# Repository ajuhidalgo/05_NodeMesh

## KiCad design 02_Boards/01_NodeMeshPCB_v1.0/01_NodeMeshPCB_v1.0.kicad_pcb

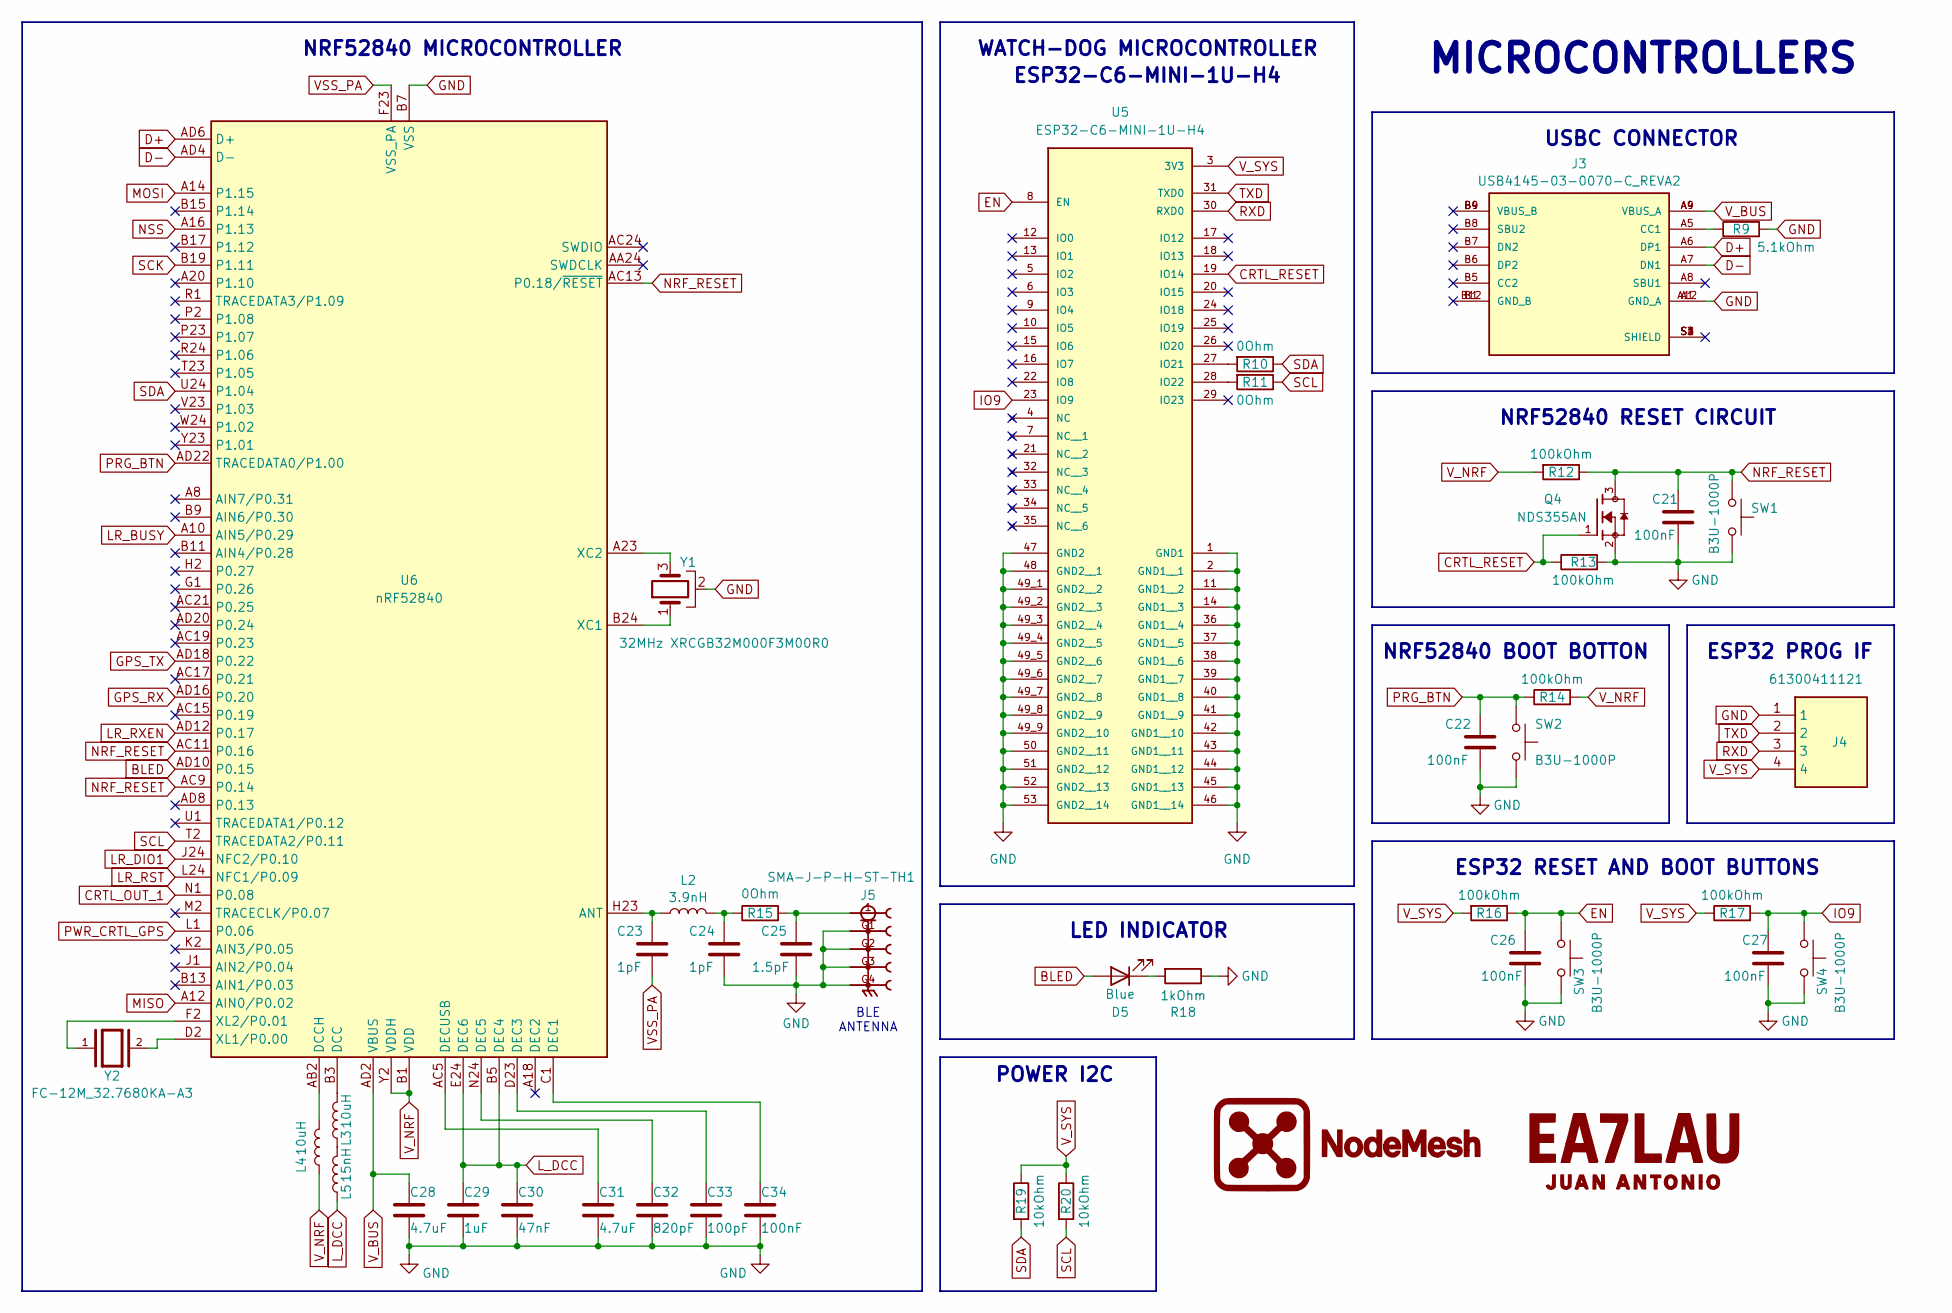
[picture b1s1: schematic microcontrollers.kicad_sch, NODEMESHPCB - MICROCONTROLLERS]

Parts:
C21, C22, C26, C27, C34: 100nF; C_0603_1608Metric
C23, C24: 1pF; C_0603_1608Metric
C25: 1.5pF; C_0603_1608Metric
C28, C31: 4.7uF; C_0603_1608Metric
C29: 1uF; C_0603_1608Metric
C30: 47nF; C_0603_1608Metric
C32: 820pF; C_0603_1608Metric
C33: 100pF; C_0603_1608Metric
D5: Blue; LED_0603_1608Metric
J3: USB4145-03-0070-C_REVA2; USB4145-03-0070-C; PARTREV A2
J4: 61300411121; Manufacturer_Part_Number 61300411121
J5: SMA-J-P-H-ST-TH1
L2: 3.9nH; L_0603_1608Metric
L3, L4: 10uH; L_0603_1608Metric
L5: 15nH; L_0603_1608Metric
Q4: NDS355AN; PARTREV 3
R9: 5.1kOhm; R_0603_1608Metric
R10, R11, R15: 0Ohm; R_0603_1608Metric
R12, R13, R14, R16, R17: 100kOhm; R_0603_1608Metric
R18: 1kOhm; R_0603_1608Metric
R19, R20: 10kOhm; R_0603_1608Metric
SW1, SW2, SW3, SW4: B3U-1000P; SW_SPST_B3U-1000P
U5: ESP32-C6-MINI-1U-H4; PARTREV 1.0
U6: nRF52840; Nordic_AQFN-73-1EP_7x7mm_P0.5mm
Y1: 32MHz XRCGB32M000F3M00R0; XRCGB32M000F3M00R0
Y2: FC-12M_32.7680KA-A3; FC-12M_327680KA-A3; PARTREV NA

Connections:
BLED: D5.2 (A), U6.AD10 (P0.15)
CRTL_OUT_1: U6.N1 (P0.08); also elsewhere on the board
CRTL_RESET: Q4.1, R13.1, U5.19 (IO14)
D+: J3.A6 (DP1), U6.AD6 (D+)
D-: J3.A7 (DN1), U6.AD4 (D-)
EN: C26.1, R16.1, SW3.1, U5.8 (EN)
GND: C21.2, C22.2, C24.2, C25.2, C26.2, C27.2, C28.2, C29.2, C30.2, C31.2, C32.2, C33.2, C34.2, J3.A1 (GND_A), J3.A12 (GND_A), J4.1, J5.G1, J5.G2, J5.G3, J5.G4, Q4.2, R9.2, R13.2, R18.1, SW1.2, SW2.2, SW3.2, SW4.2, U5.1 (GND1), U5.2 (GND1__1), U5.11 (GND1__2), U5.14 (GND1__3), U5.36 (GND1__4), U5.37 (GND1__5), U5.38 (GND1__6), U5.39 (GND1__7), U5.40 (GND1__8), U5.41 (GND1__9), U5.42 (GND1__10), U5.43 (GND1__11), U5.44 (GND1__12), U5.45 (GND1__13), U5.46 (GND1__14), U5.47 (GND2), U5.48 (GND2__1), U5.49_1 (GND2__2), U5.49_2 (GND2__3), U5.49_3 (GND2__4), U5.49_4 (GND2__5), U5.49_5 (GND2__6), U5.49_6 (GND2__7), U5.49_7 (GND2__8), U5.49_8 (GND2__9), U5.49_9 (GND2__10), U5.50 (GND2__11), U5.51 (GND2__12), U5.52 (GND2__13), U5.53 (GND2__14), U6.B7 (VSS), U6.EP (VSS), Y1.2; also elsewhere on the board
GPS_RX: U6.AD16 (P0.20); also elsewhere on the board
GPS_TX: U6.AD18 (P0.22); also elsewhere on the board
IO9: C27.1, R17.2, SW4.1, U5.23 (IO9)
LR_BUSY: U6.A10 (AIN5/P0.29); also elsewhere on the board
LR_DIO1: U6.J24 (NFC2/P0.10); also elsewhere on the board
LR_RST: U6.L24 (NFC1/P0.09); also elsewhere on the board
LR_RXEN: U6.AD12 (P0.17); also elsewhere on the board
L_DCC: C29.1, C30.1, L5.1, U6.B5 (DEC4), U6.E24 (DEC6)
MISO: U6.A12 (AIN0/P0.02); also elsewhere on the board
MOSI: U6.A14 (P1.15); also elsewhere on the board
NRF_RESET: C21.1, Q4.3, R12.1, SW1.1, U6.AC9 (P0.14), U6.AC11 (P0.16), U6.AC13 (P0.18/~RESET)
NSS: U6.A16 (P1.13); also elsewhere on the board
unnamed: C24.1, L2.2, R15.1
unnamed: C25.1, J5.1, R15.2
unnamed: D5.1 (K), R18.2
unnamed: J3.A5 (CC1), R9.1
unnamed: L3.1, L5.2
unnamed: R10.2, U5.27 (IO21)
unnamed: R11.2, U5.28 (IO22)
unnamed: C23.1, L2.1, U6.H23 (ANT)
unnamed: L3.2, U6.B3 (DCC)
unnamed: L4.2, U6.AB2 (DCCH)
unnamed: C34.1, U6.C1 (DEC1)
unnamed: C33.1, U6.D23 (DEC3)
unnamed: C32.1, U6.N24 (DEC5)
unnamed: C31.1, U6.AC5 (DECUSB)
unnamed: U6.B24 (XC1), Y1.1
unnamed: U6.A23 (XC2), Y1.3
unnamed: U6.D2 (XL1/P0.00), Y2.2
unnamed: U6.F2 (XL2/P0.01), Y2.1
PRG_BTN: C22.1, R14.1, SW2.1, U6.AD22 (TRACEDATA0/P1.00)
PWR_CRTL_GPS: U6.L1 (P0.06); also elsewhere on the board
RXD: J4.3, U5.30 (RXD0)
SCK: U6.B19 (P1.11); also elsewhere on the board
SCL: R11.1, R20.2, U6.T2 (TRACEDATA2/P0.11); also elsewhere on the board
SDA: R10.1, R19.2, U6.U24 (P1.04); also elsewhere on the board
TXD: J4.2, U5.31 (TXD0)
VSS_PA: C23.2, U6.F23 (VSS_PA)
V_BUS: C28.1, J3.A4 (VBUS_A), J3.A9 (VBUS_A), U6.AD2 (VBUS)
V_NRF: J4.4, L4.1, R12.2, R14.2, R16.2, R17.1, R19.1, R20.1, U5.3 (3V3), U6.A22 (VDD), U6.AD14 (VDD), U6.AD23 (VDD), U6.B1 (VDD), U6.W1 (VDD), U6.Y2 (VDDH); also elsewhere on the board

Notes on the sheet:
USBC CONNECTOR
ESP32-C6-MINI-1U-H4
NRF52840 MICROCONTROLLER
ESP32 RESET AND BOOT BUTTONS
WATCH-DOG MICROCONTROLLER
POWER I2C
LED INDICATOR
NRF52840 RESET CIRCUIT
ESP32 PROG IF
MICROCONTROLLERS
NRF52840 BOOT BOTTON
BLE ANTENNA

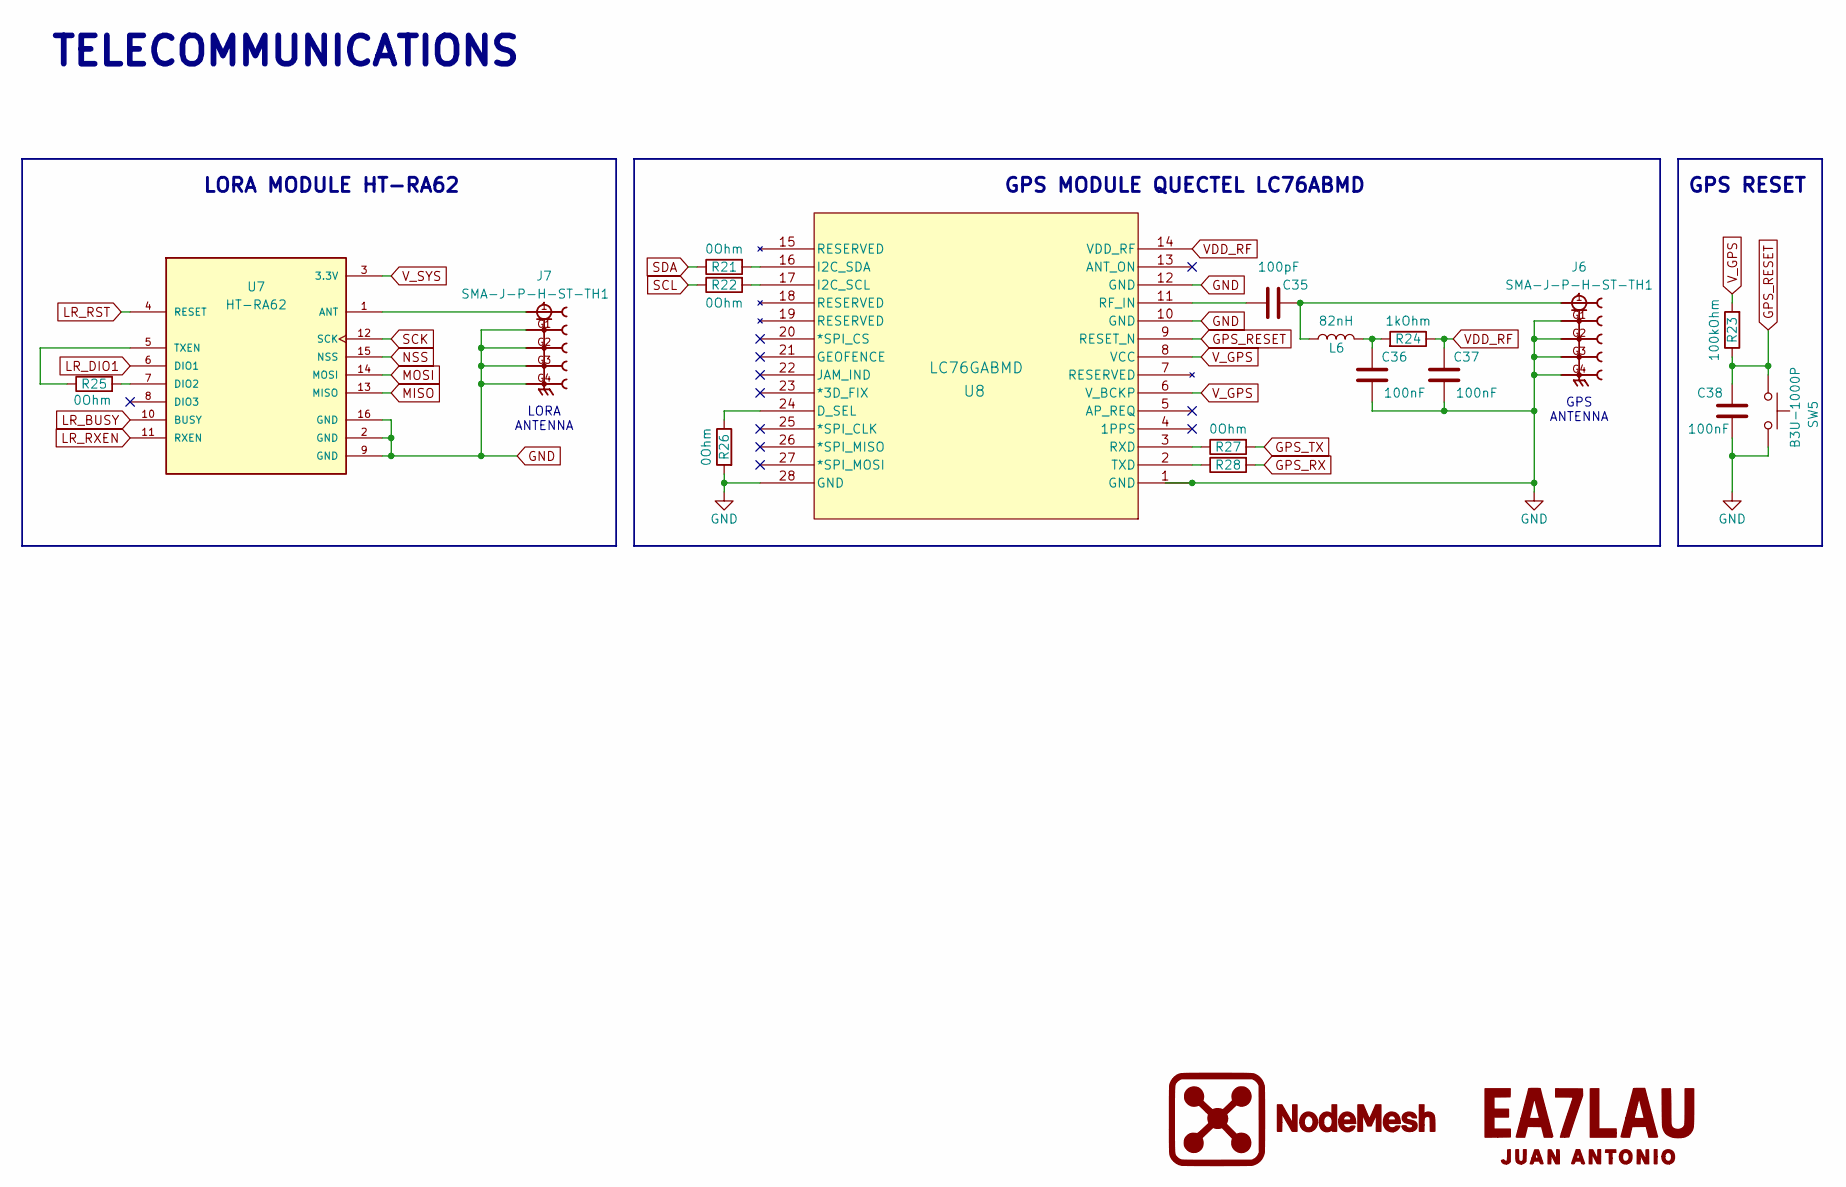
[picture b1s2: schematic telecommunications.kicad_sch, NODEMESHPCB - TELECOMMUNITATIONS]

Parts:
C35: 100pF; C_0603_1608Metric
C36, C37, C38: 100nF; C_0603_1608Metric
J6, J7: SMA-J-P-H-ST-TH1
L6: 82nH; L_0603_1608Metric
R21, R22, R25, R26, R27, R28: 0Ohm; R_0603_1608Metric
R23: 100kOhm; R_0603_1608Metric
R24: 1kOhm; R_0603_1608Metric
SW5: B3U-1000P; SW_SPST_B3U-1000P
U7: HT-RA62
U8: LC76GABMD

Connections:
GND: C36.2, C37.2, C38.2, J6.G1, J6.G2, J6.G3, J6.G4, J7.G1, J7.G2, J7.G3, J7.G4, R26.2, SW5.2, U7.2 (GND), U7.9 (GND), U7.16 (GND), U8.1 (GND), U8.10 (GND), U8.12 (GND), U8.28 (GND); also elsewhere on the board
GPS_RESET: C38.1, R23.1, SW5.1, U8.9 (RESET_N)
GPS_RX: R28.2; also elsewhere on the board
GPS_TX: R27.2; also elsewhere on the board
LR_BUSY: U7.10 (BUSY); also elsewhere on the board
LR_DIO1: U7.6 (DIO1); also elsewhere on the board
LR_RST: U7.4 (RESET); also elsewhere on the board
LR_RXEN: U7.11 (RXEN); also elsewhere on the board
MISO: U7.13 (MISO); also elsewhere on the board
MOSI: U7.14 (MOSI); also elsewhere on the board
NSS: U7.15 (NSS); also elsewhere on the board
unnamed: C35.2, J6.1, L6.2
unnamed: C36.1, L6.1, R24.2
unnamed: J7.1, U7.1 (ANT)
unnamed: R25.2, U7.7 (DIO2)
unnamed: R25.1, U7.5 (TXEN)
unnamed: R26.1, U8.24 (D_SEL)
unnamed: R22.2, U8.17 (I2C_SCL)
unnamed: R21.2, U8.16 (I2C_SDA)
unnamed: C35.1, U8.11 (RF_IN)
unnamed: R27.1, U8.3 (RXD)
unnamed: R28.1, U8.2 (TXD)
SCK: U7.12 (SCK); also elsewhere on the board
SCL: R22.1; also elsewhere on the board
SDA: R21.1; also elsewhere on the board
VDD_RF: C37.1, R24.1, U8.14 (VDD_RF)
V_GPS: R23.2, U8.6 (V_BCKP), U8.8 (VCC); also elsewhere on the board
V_NRF: U7.3 (3.3V); also elsewhere on the board

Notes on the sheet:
LORA ANTENNA
GPS MODULE QUECTEL LC76ABMD
LORA MODULE HT-RA62
GPS RESET
GPS ANTENNA
TELECOMMUNICATIONS

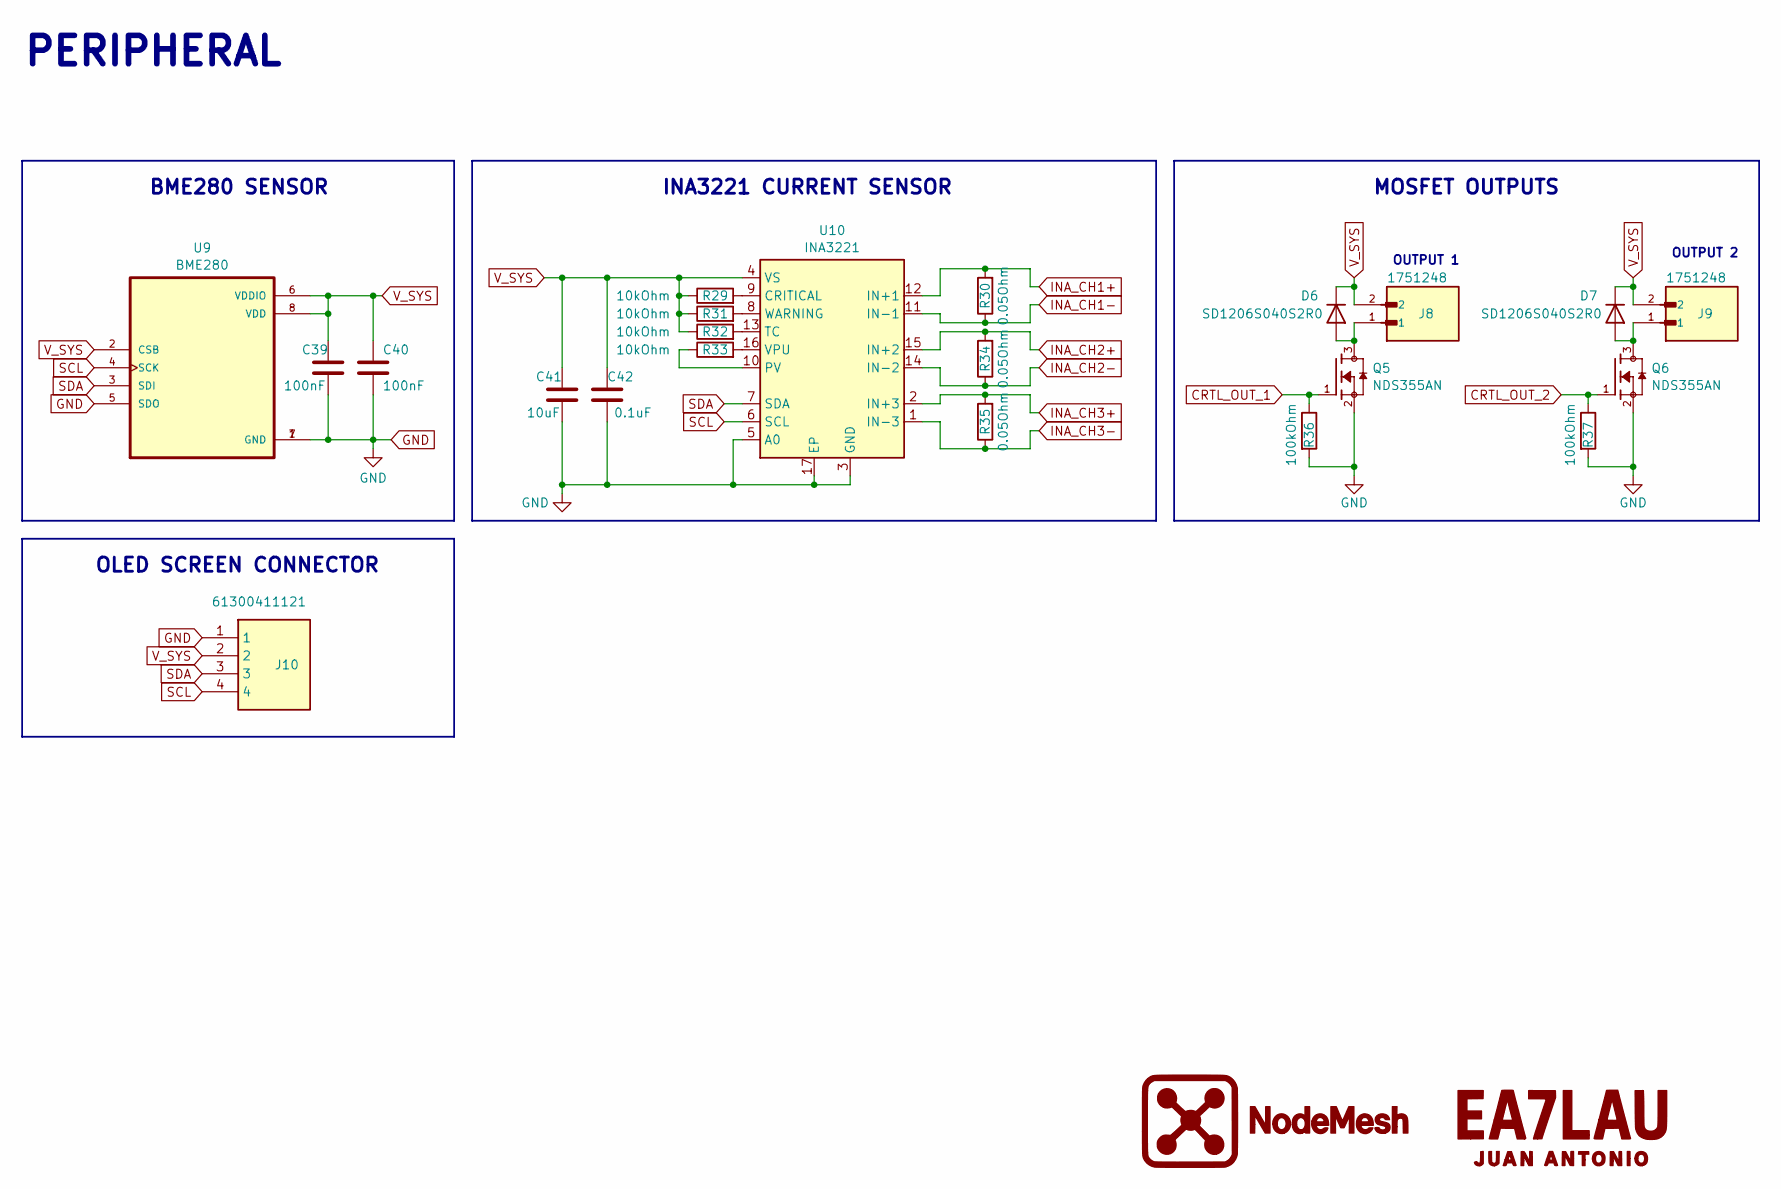
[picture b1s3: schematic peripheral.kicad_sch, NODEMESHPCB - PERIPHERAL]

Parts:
C39, C40: 100nF; C_0603_1608Metric
C41: 10uF; C_0603_1608Metric
C42: 0.1uF; C_0603_1608Metric
D6, D7: SD1206S040S2R0; D_1206_3216Metric
J8, J9: 1751248; TerminalBlock_Phoenix_MKDS-1,5-2-5.08_1x02_P5.08mm_Horizont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
J10: 61300411121; Manufacturer_Part_Number 61300411121
Q5, Q6: NDS355AN; PARTREV 3
R29, R31, R32, R33: 10kOhm; R_0603_1608Metric
R30, R34, R35: 0.05Ohm; R_1206_3216Metric
R36, R37: 100kOhm; R_0603_1608Metric
U9: BME280
U10: INA3221

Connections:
CRTL_OUT_1: Q5.1, R36.1; also elsewhere on the board
CRTL_OUT_2: Q6.1, R37.1
GND: C39.2, C40.2, C41.2, C42.2, J10.1, Q5.2, Q6.2, R36.2, R37.2, U9.1 (GND), U9.5 (SDO), U9.7 (GND), U10.3 (GND), U10.5 (A0), U10.17 (EP); also elsewhere on the board
INA_CH1+: R30.2, R34.1, U10.12 (IN+1), U10.14 (IN-2); also elsewhere on the board
INA_CH1-: R30.1, U10.11 (IN-1); also elsewhere on the board
INA_CH2+: R34.2, U10.15 (IN+2); also elsewhere on the board
INA_CH3+: R35.2, U10.2 (IN+3); also elsewhere on the board
INA_CH3-: R35.1, U10.1 (IN-3); also elsewhere on the board
unnamed: D6.2 (A), J8.1, Q5.3
unnamed: D7.2 (A), J9.1, Q6.3
unnamed: R29.2, U10.9 (CRITICAL)
unnamed: R33.1, U10.10 (PV)
unnamed: R32.2, U10.13 (TC)
unnamed: R33.2, U10.16 (VPU)
unnamed: R31.2, U10.8 (WARNING)
SCL: J10.4, U9.4 (SCK), U10.6 (SCL); also elsewhere on the board
SDA: J10.3, U9.3 (SDI), U10.7 (SDA); also elsewhere on the board
V_NRF: C39.1, C40.1, C41.1, C42.1, D6.1 (K), D7.1 (K), J8.2, J9.2, J10.2, R29.1, R31.1, R32.1, U9.2 (CSB), U9.6 (VDDIO), U9.8 (VDD), U10.4 (VS); also elsewhere on the board

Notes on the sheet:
BME280 SENSOR
OUTPUT 1
INA3221 CURRENT SENSOR
OUTPUT 2
MOSFET OUTPUTS
OLED SCREEN CONNECTOR
PERIPHERAL

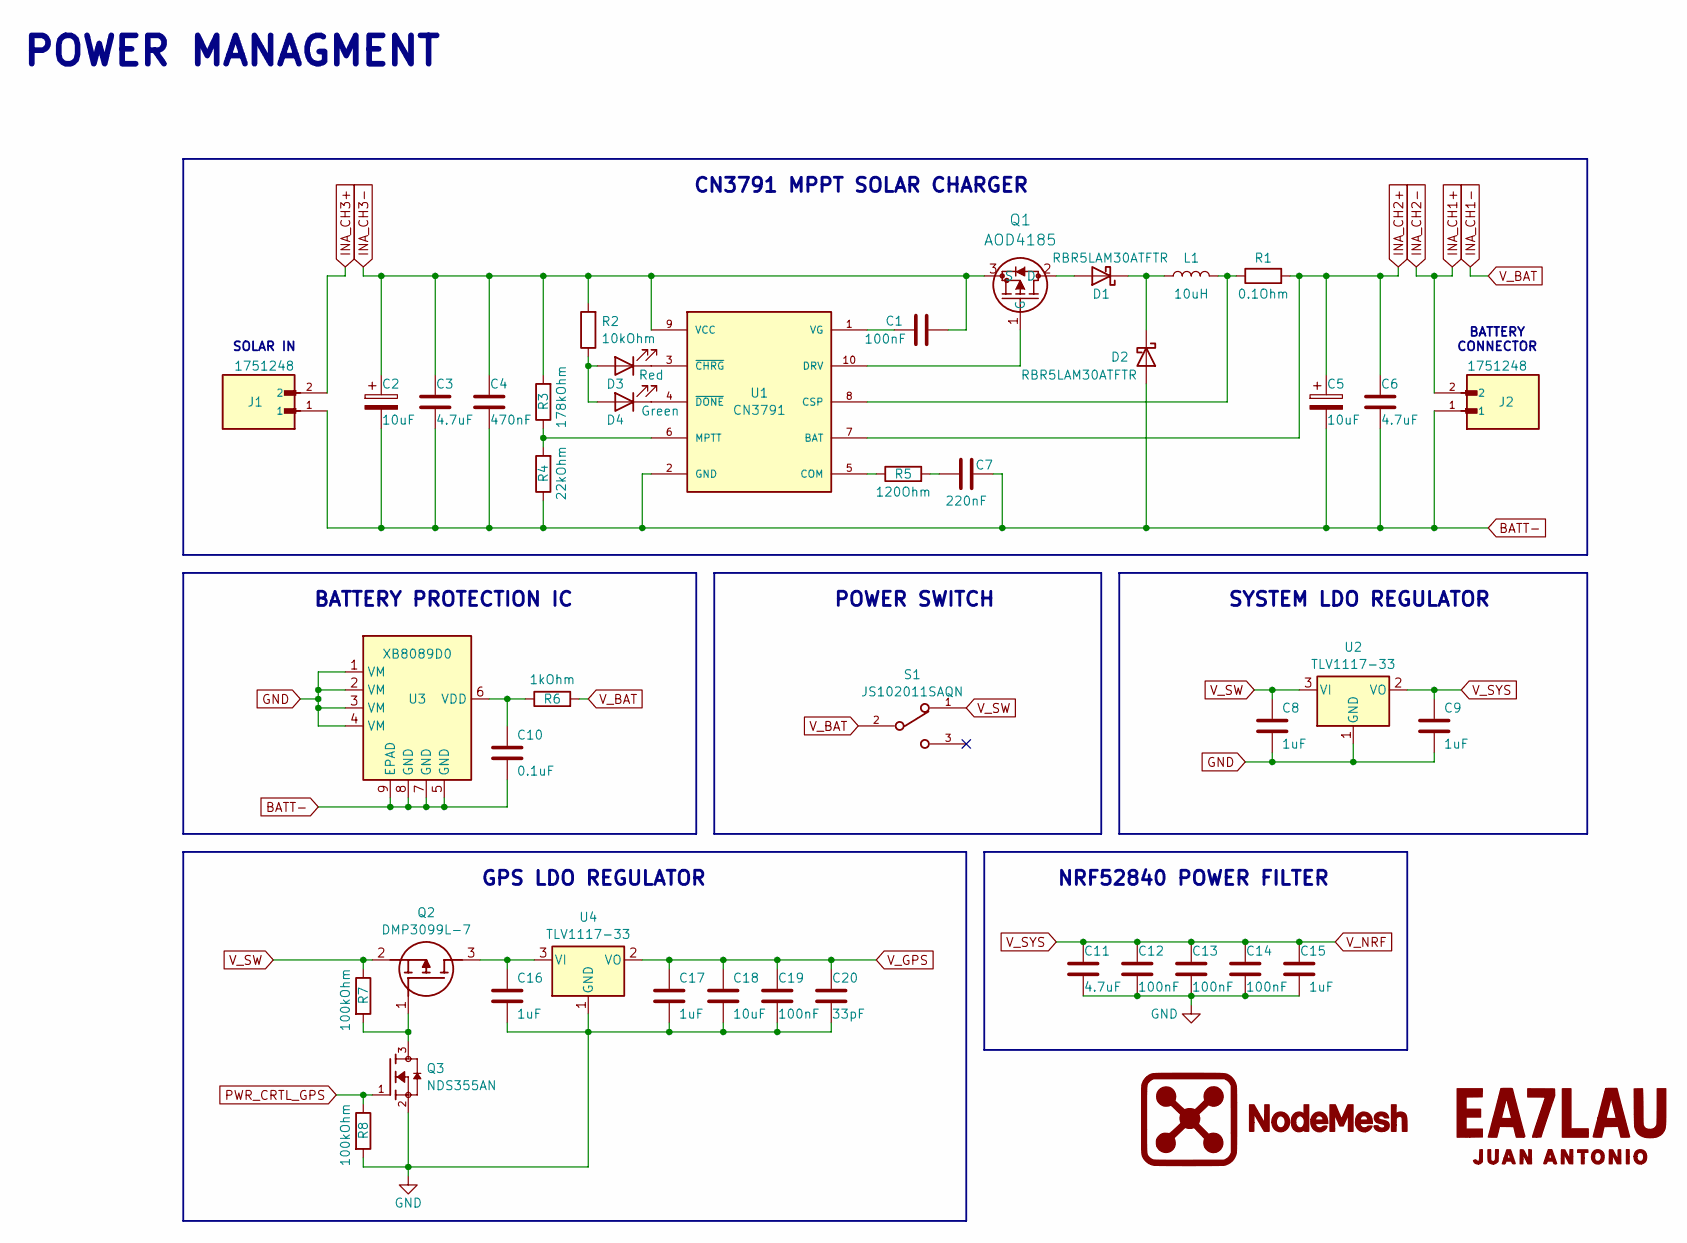
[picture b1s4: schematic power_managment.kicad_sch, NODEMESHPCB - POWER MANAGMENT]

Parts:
C1, C12, C13, C14, C19: 100nF; C_0603_1608Metric
C2, C5, C18: 10uF; C_0603_1608Metric
C3, C6, C11: 4.7uF; C_0603_1608Metric
C4: 470nF; C_0603_1608Metric
C7: 220nF; C_0603_1608Metric
C8, C9, C15, C16, C17: 1uF; C_0603_1608Metric
C10: 0.1uF; C_0603_1608Metric
C20: 33pF; C_0603_1608Metric
D1, D2: RBR5LAM30ATFTR
D3: Red; LED_0603_1608Metric
D4: Green; LED_0603_1608Metric
J1, J2: 1751248; TerminalBlock_Phoenix_MKDS-1,5-2-5.08_1x02_P5.08mm_Horizont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
L1: 10uH; L_0603_1608Metric
Q1: AOD4185
Q2: DMP3099L-7; Mouser Part Number 621-DMP3099L-7
Q3: NDS355AN; PARTREV 3
R1: 0.1Ohm; R_1206_3216Metric
R2: 10kOhm; R_0603_1608Metric
R3: 178kOhm; R_0603_1608Metric
R4: 22kOhm; R_0603_1608Metric
R5: 120Ohm; R_0603_1608Metric
R6: 1kOhm; R_0603_1608Metric
R7, R8: 100kOhm; R_0603_1608Metric
S1: JS102011SAQN
U1: CN3791
U2, U4: TLV1117-33; TLV1117LV33DCYR
U3: XB8089D0

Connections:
BATT-: C2.2, C3.2, C4.2, C5.2, C6.2, C7.2, C10.2, D2.2 (A), J1.1, J2.1, R4.1, U1.2 (GND), U3.5 (GND), U3.7 (GND), U3.8 (GND), U3.9 (EPAD)
GND: C8.2, C9.2, C11.2, C12.2, C13.2, C14.2, C15.2, C16.2, C17.2, C18.2, C19.2, C20.2, Q3.2, R8.2, U2.1 (GND), U3.1 (VM), U3.2 (VM), U3.3 (VM), U3.4 (VM), U4.1 (GND); also elsewhere on the board
INA_CH1+: J2.2; also elsewhere on the board
INA_CH1-: R6.2, S1.2; also elsewhere on the board
INA_CH2+: C5.1, C6.1, R1.2, U1.7 (BAT); also elsewhere on the board
INA_CH3+: J1.2; also elsewhere on the board
INA_CH3-: C1.2, C2.1, C3.1, C4.1, Q1.3 (S), R2.2, R3.2, U1.9 (VCC); also elsewhere on the board
unnamed: C7.1, R5.2
unnamed: D1.2 (A), Q1.2 (D)
unnamed: D1.1 (K), D2.1 (K), L1.1
unnamed: D3.2 (A), D4.2 (A), R2.1
unnamed: D3.1 (K), U1.3 (~CHRG)
unnamed: D4.1 (K), U1.4 (~DONE)
unnamed: Q1.1 (G), U1.10 (DRV)
unnamed: C16.1, Q2.3 (D), U4.3 (VI)
unnamed: Q2.1 (G), Q3.3, R7.2
unnamed: R5.1, U1.5 (COM)
unnamed: L1.2, R1.1, U1.8 (CSP)
unnamed: R3.1, R4.2, U1.6 (MPTT)
unnamed: C1.1, U1.1 (VG)
unnamed: C10.1, R6.1, U3.6 (VDD)
PWR_CRTL_GPS: Q3.1, R8.1; also elsewhere on the board
V_GPS: C17.1, C18.1, C19.1, C20.1, U4.2 (VO); also elsewhere on the board
V_NRF: C9.1, C11.1, C12.1, C13.1, C14.1, C15.1, U2.2 (VO); also elsewhere on the board
V_SW: C8.1, Q2.2 (S), R7.1, S1.1, U2.3 (VI)

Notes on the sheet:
CN3791 MPPT SOLAR CHARGER
GPS LDO REGULATOR
NRF52840 POWER FILTER
SOLAR IN
SYSTEM LDO REGULATOR
BATTERY CONNECTOR
POWER SWITCH
BATTERY PROTECTION IC
POWER MANAGMENT

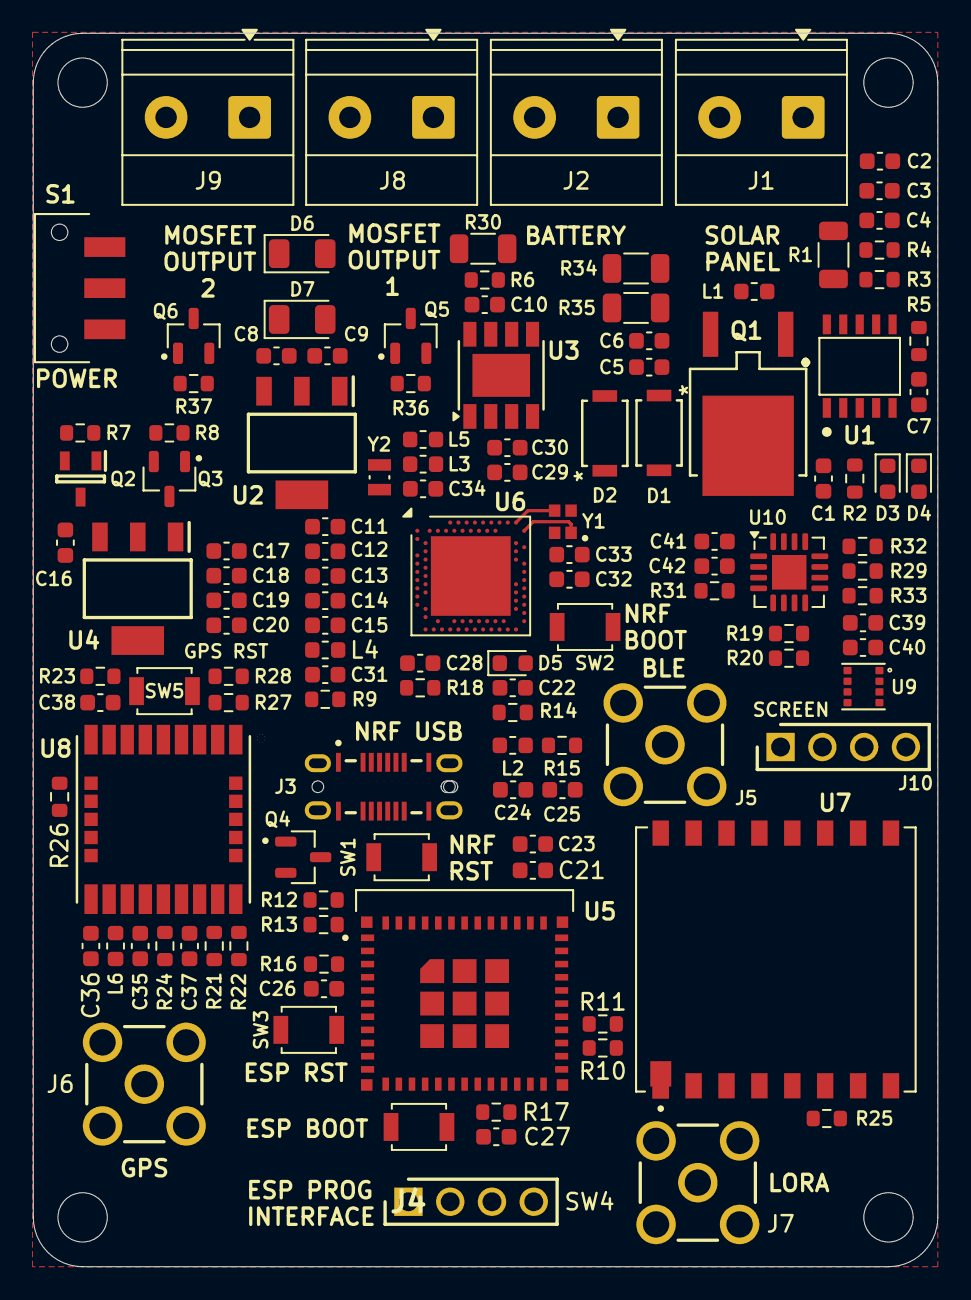
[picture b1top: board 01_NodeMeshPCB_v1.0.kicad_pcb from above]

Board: 4 copper layers, 55.0 x 75.0 mm, 126 parts (0 on the bottom side), 90 nets.

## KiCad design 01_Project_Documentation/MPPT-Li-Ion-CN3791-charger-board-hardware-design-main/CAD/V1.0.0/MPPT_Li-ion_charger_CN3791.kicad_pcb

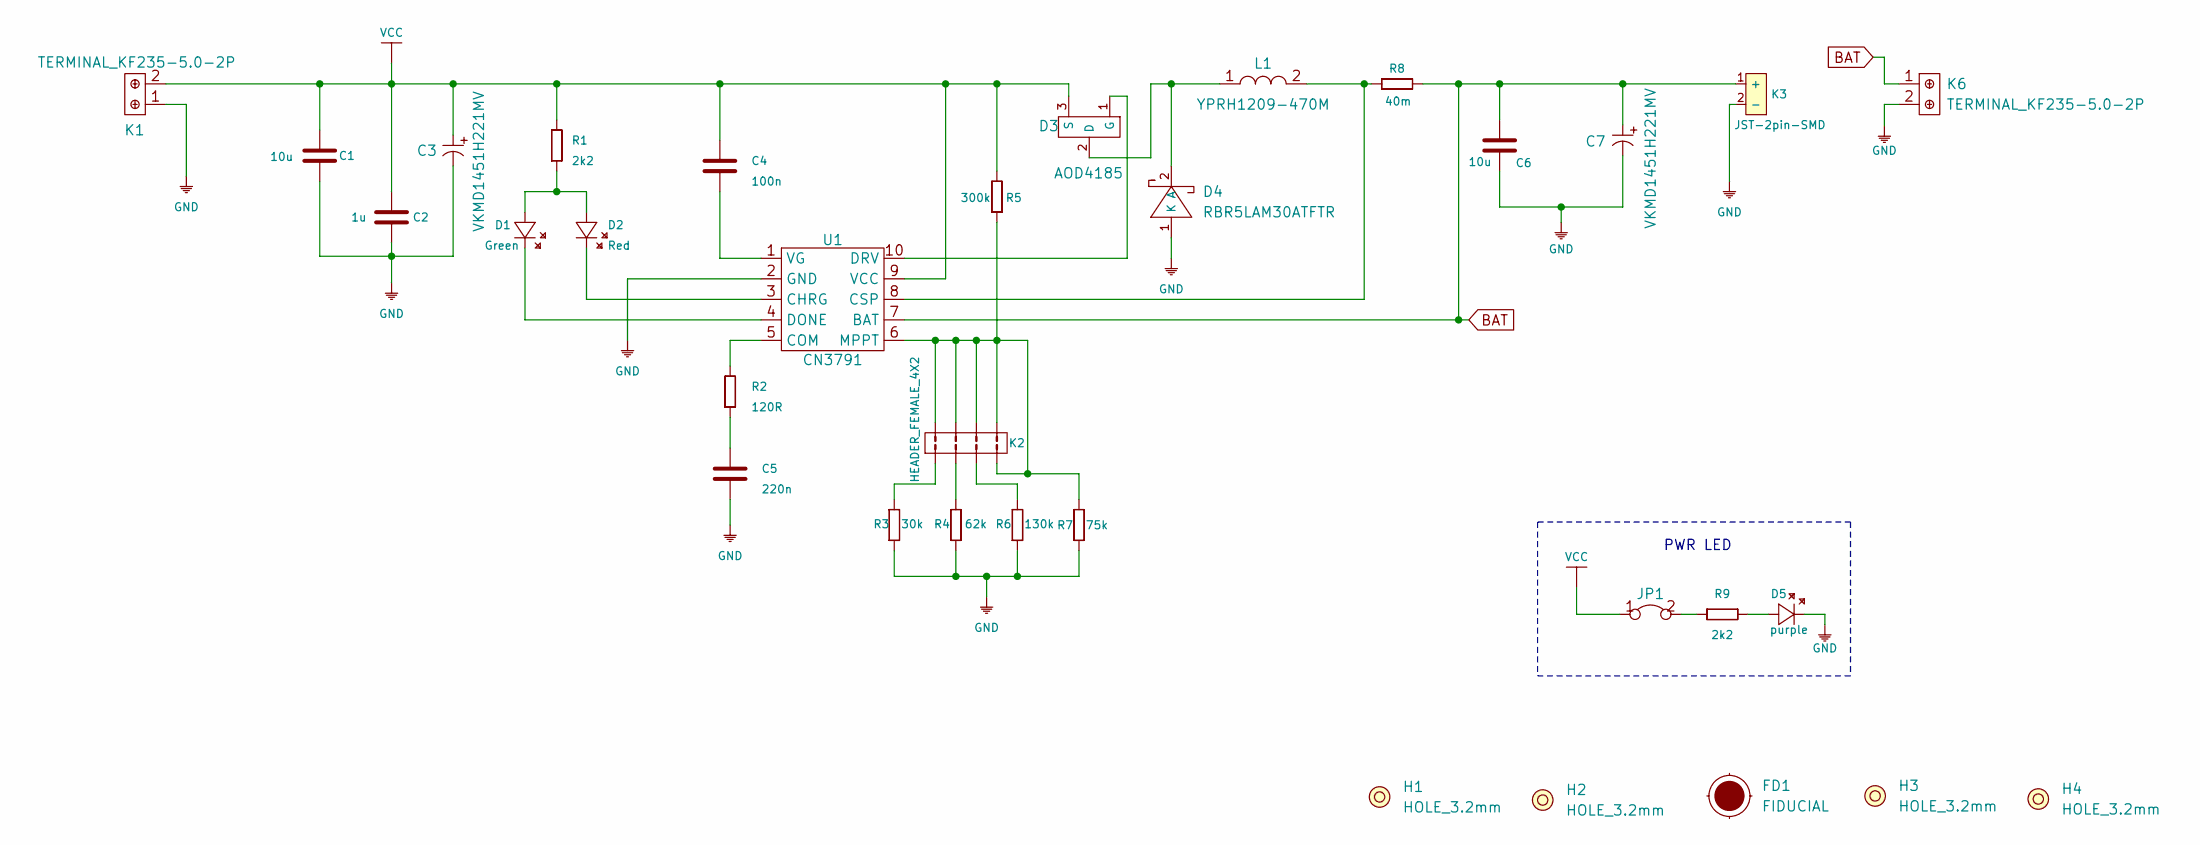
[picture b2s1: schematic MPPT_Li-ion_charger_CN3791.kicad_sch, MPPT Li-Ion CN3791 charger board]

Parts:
C1, C6: 10u; 1206C
C2: 1u; 0603C
C3, C7: VKMD1451H221MV; ELECTROLITIC_CAP_8x8x14.5
C4: 100n; 0603C
C5: 220n; 0603C
D1: Green; 0402LED
D2: Red; 0402LED
D3: AOD4185; DPAK
D4: RBR5LAM30ATFTR
D5: purple; 0402LED
FD1: FIDUCIAL; FIDUCIAL_23
H1, H2, H3, H4: HOLE_3.2mm
JP1: SMD-JUMPER-CONNECTED_TRACE_SLODERMASK
K1, K6: TERMINAL_KF235-5.0-2P
K2: HEADER_FEMALE_4X2
K3: JST-2pin-SMD
L1: YPRH1209-470M
R1, R9: 2k2; 0402R
R2: 120R; 0603R
R3: 30k; 0603R
R4: 62k; 0603R
R5: 300k; 0603R
R6: 130k; 0603R
R7: 75k; 0603R
R8: 40m; 1210R
U1: CN3791

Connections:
BAT: C6.2, C7.1 (+), K3.1 (+), K6.1, R8.2, U1.7 (BAT)
GND: C1.1, C2.1, C3.2 (-), C5.1, C6.1, C7.2 (-), D4.1 (K), D5.2 (K), K1.1, K3.2 (-), K6.2, R3.1, R4.1, R6.1, R7.1, U1.2 (GND)
unnamed: C4.1, U1.1 (VG)
unnamed: C5.2, R2.1
unnamed: D1.1 (A), D2.1 (A), R1.1
unnamed: D1.2 (K), U1.4 (DONE)
unnamed: D2.2 (K), U1.3 (CHRG)
unnamed: D3.1 (G), U1.10 (DRV)
unnamed: D3.2 (D), D4.2 (A), L1.1
unnamed: D5.1 (A), R9.2
unnamed: JP1.2, R9.1
unnamed: K2.1, R3.2
unnamed: K2.2, R4.2
unnamed: K2.3, R6.2
unnamed: K2.4, K2.5, K2.6, K2.7, K2.8, R5.1, R7.2, U1.6 (MPPT)
unnamed: L1.2, R8.1, U1.8 (CSP)
unnamed: R2.2, U1.5 (COM)
VCC: C1.2, C2.2, C3.1 (+), C4.2, D3.3 (S), JP1.1, K1.2, R1.2, R5.2, U1.9 (VCC)

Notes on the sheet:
PWR LED

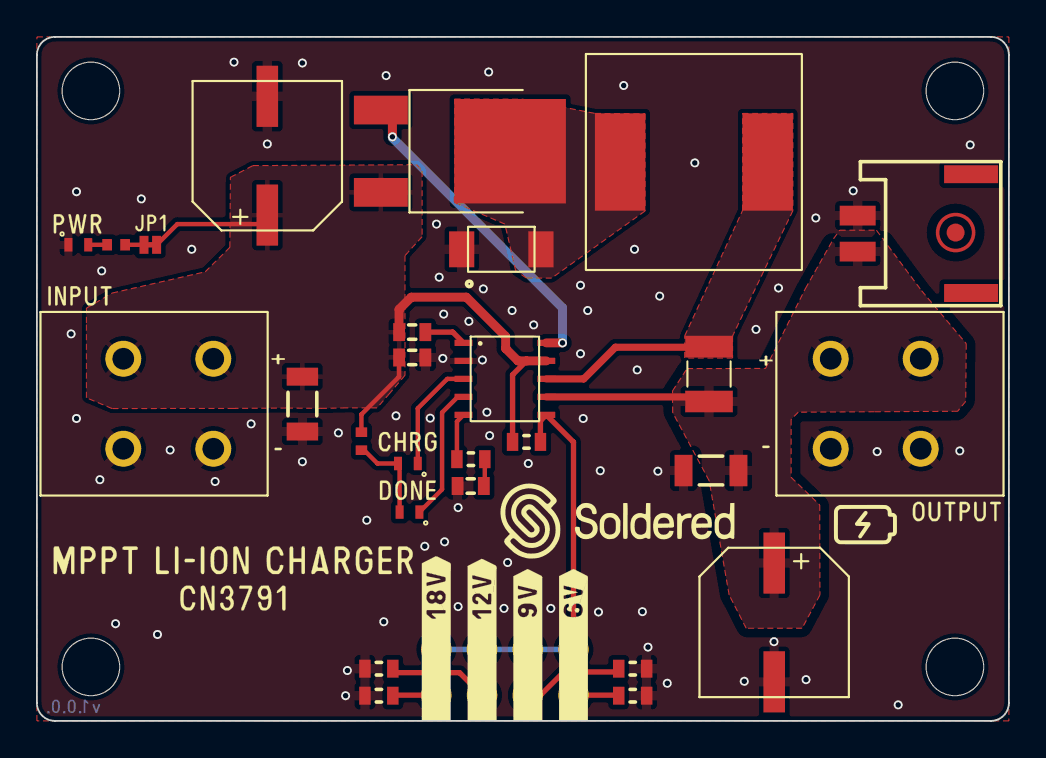
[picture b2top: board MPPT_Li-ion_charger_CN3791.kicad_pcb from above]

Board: 2 copper layers, 54.0 x 38.0 mm, 34 parts (1 on the bottom side), 18 nets.

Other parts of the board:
Ref**: Val**; Version1.0.0.

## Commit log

2025-06-18 Git Init
2025-06-19 INA3221 schematic
2025-06-22 mppt solar charger schematic
2025-06-23 3V3 LDO Schematic
2025-06-24 Battery protection and measure schematics
2025-06-25 Control Mosfets Shematic
2025-06-28 ht-ra62 schematic
2025-06-28 firmware project creation
2025-07-10 nRF52840 schematic
2026-04-21 PCB placement
